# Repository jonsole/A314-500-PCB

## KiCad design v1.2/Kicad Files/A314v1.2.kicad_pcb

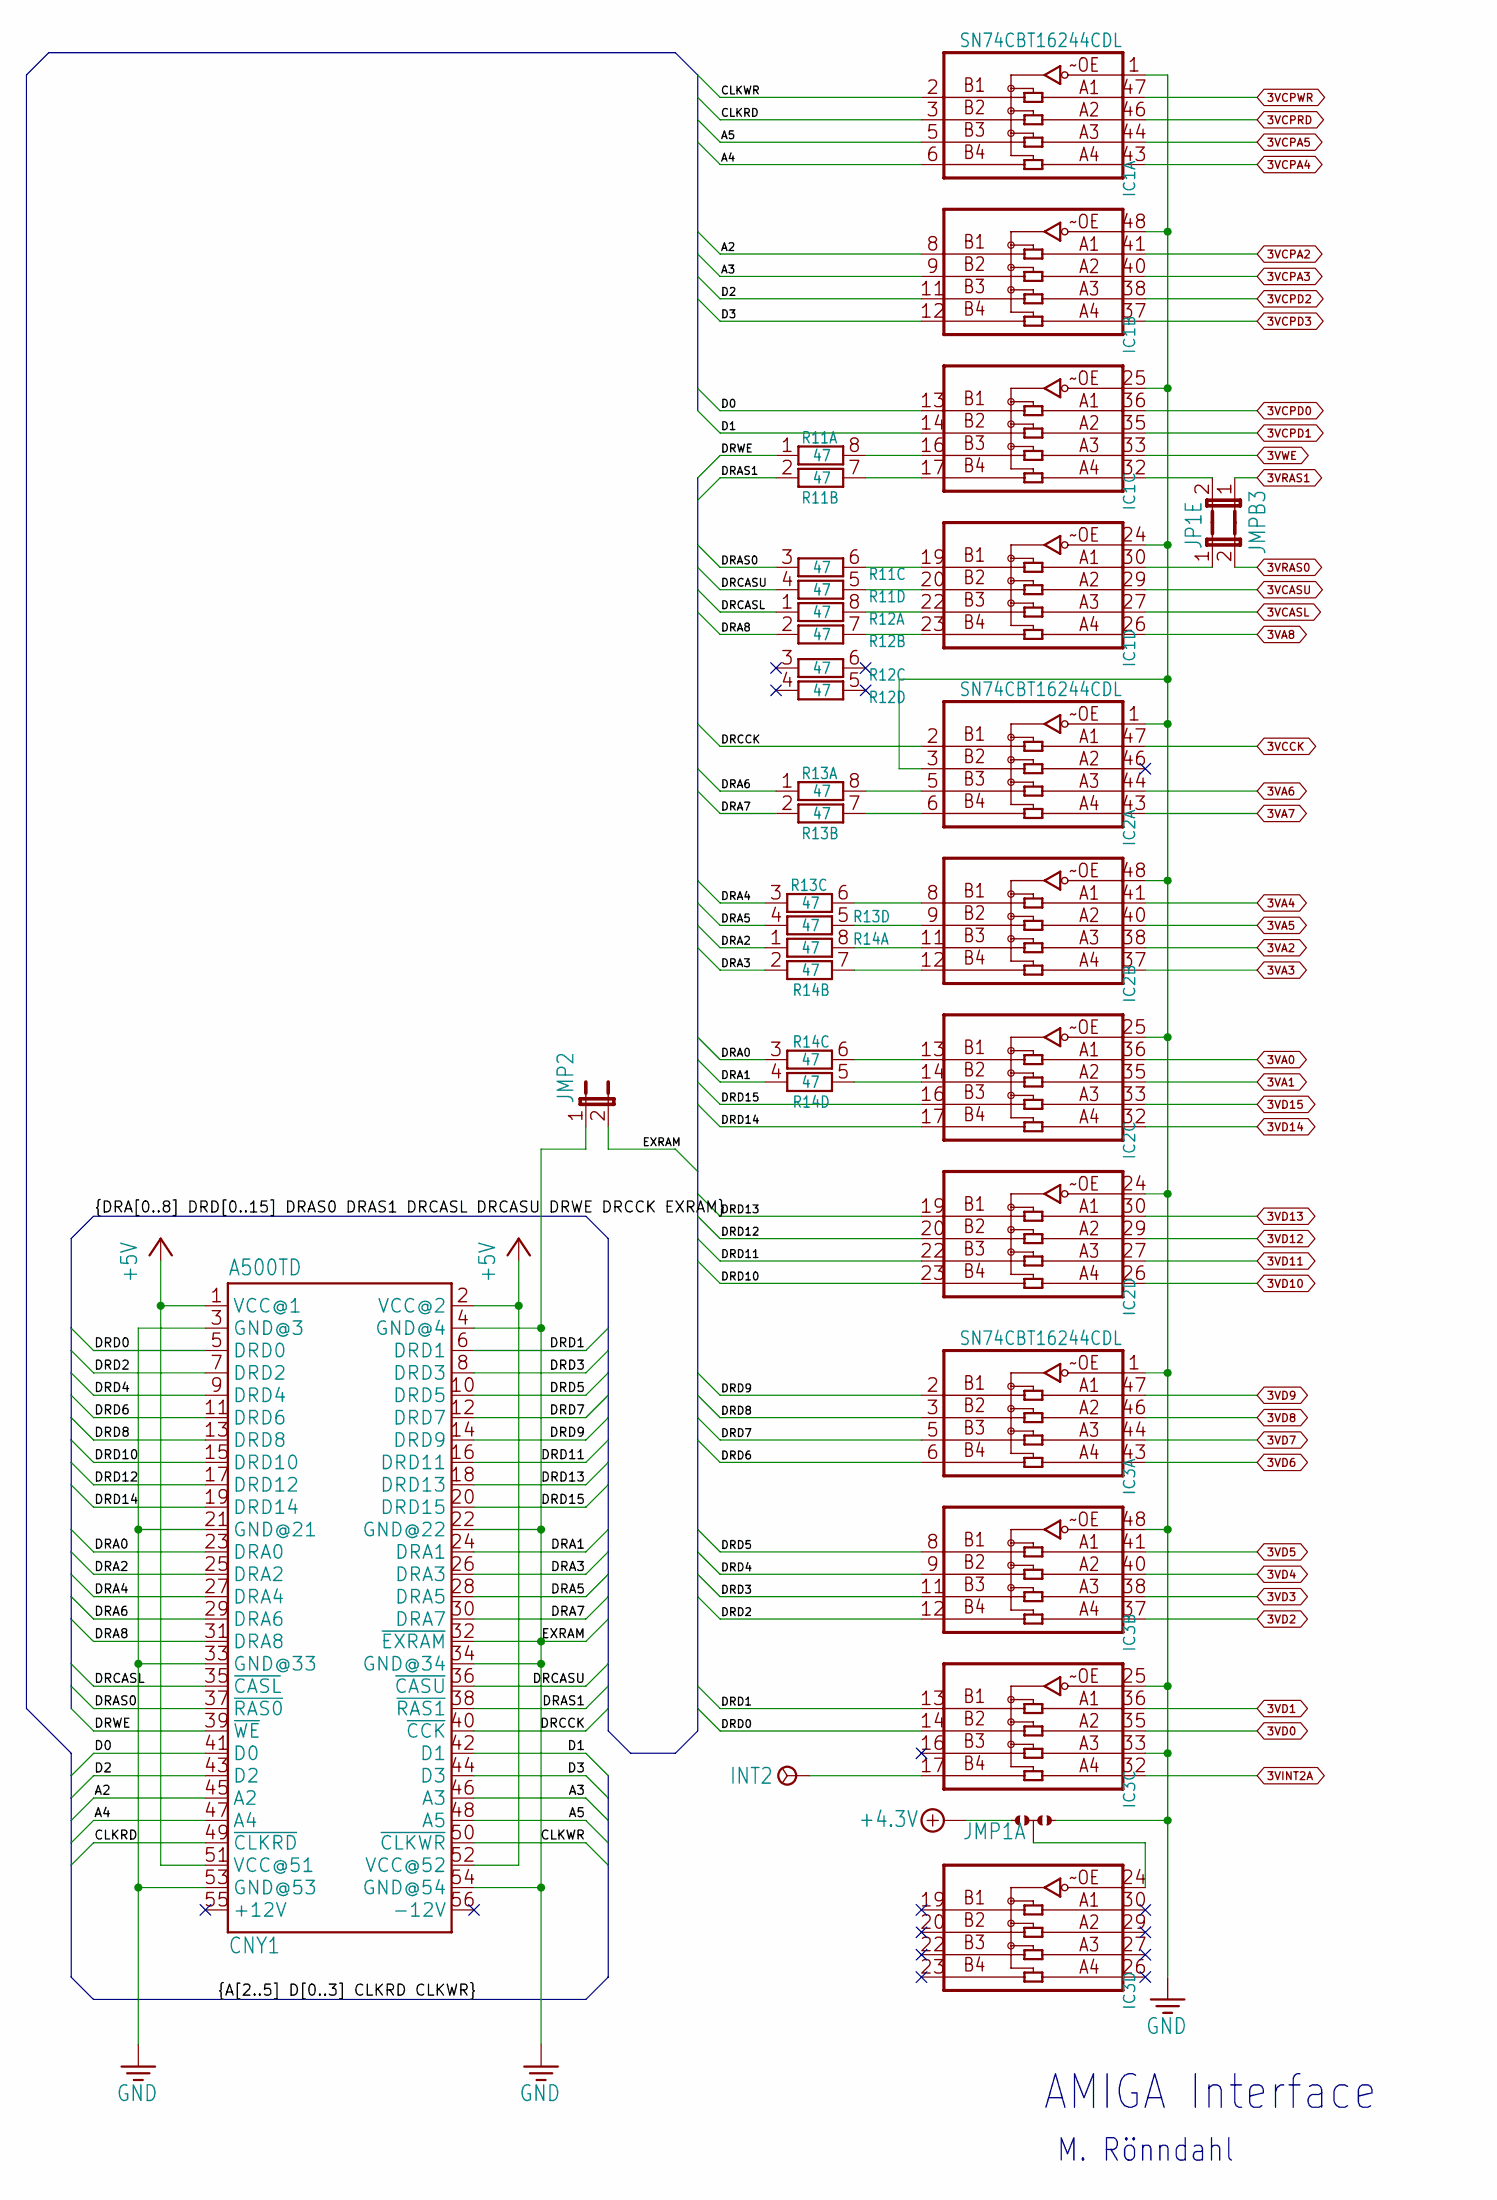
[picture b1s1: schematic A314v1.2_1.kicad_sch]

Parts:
CNY1: A500TD; TRAPDOOR
IC1, IC2, IC3: SN74CBT16244CDL; SSOP-DL48
INT2: TP1; P1-08
JMP1: 0R-JUMPC; C0R-JMP
JMP2: JP1E; JP1
JMP3: RAS0; JP1
JMPB3: JP1E; JP1
R11, R12, R13, R14: 47; CTS742C083

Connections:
3VA0: IC2.36 (A1); also elsewhere on the board
3VA1: IC2.35 (A2); also elsewhere on the board
3VA2: IC2.38 (A3); also elsewhere on the board
3VA3: IC2.37 (A4); also elsewhere on the board
3VA4: IC2.41 (A1); also elsewhere on the board
3VA5: IC2.40 (A2); also elsewhere on the board
3VA6: IC2.44 (A3); also elsewhere on the board
3VA7: IC2.43 (A4); also elsewhere on the board
3VA8: IC1.26 (A4); also elsewhere on the board
3VCASL: IC1.27 (A3); also elsewhere on the board
3VCASU: IC1.29 (A2); also elsewhere on the board
3VCCK: IC2.47 (A1); also elsewhere on the board
3VCPA2: IC1.41 (A1); also elsewhere on the board
3VCPA3: IC1.40 (A2); also elsewhere on the board
3VCPA4: IC1.43 (A4); also elsewhere on the board
3VCPA5: IC1.44 (A3); also elsewhere on the board
3VCPD0: IC1.36 (A1); also elsewhere on the board
3VCPD1: IC1.35 (A2); also elsewhere on the board
3VCPD2: IC1.38 (A3); also elsewhere on the board
3VCPD3: IC1.37 (A4); also elsewhere on the board
3VCPRD: IC1.46 (A2); also elsewhere on the board
3VCPWR: IC1.47 (A1); also elsewhere on the board
3VD0: IC3.35 (A2); also elsewhere on the board
3VD1: IC3.36 (A1); also elsewhere on the board
3VD2: IC3.37 (A4); also elsewhere on the board
3VD3: IC3.38 (A3); also elsewhere on the board
3VD4: IC3.40 (A2); also elsewhere on the board
3VD5: IC3.41 (A1); also elsewhere on the board
3VD6: IC3.43 (A4); also elsewhere on the board
3VD7: IC3.44 (A3); also elsewhere on the board
3VD8: IC3.46 (A2); also elsewhere on the board
3VD9: IC3.47 (A1); also elsewhere on the board
3VD10: IC2.26 (A4); also elsewhere on the board
3VD11: IC2.27 (A3); also elsewhere on the board
3VD12: IC2.29 (A2); also elsewhere on the board
3VD13: IC2.30 (A1); also elsewhere on the board
3VD14: IC2.32 (A4); also elsewhere on the board
3VD15: IC2.33 (A3); also elsewhere on the board
3VINT2A: IC3.32 (A4); also elsewhere on the board
3VRAS0: JMP3.2; also elsewhere on the board
3VRAS1: JMPB3.1; also elsewhere on the board
3VWE: IC1.33 (A3); also elsewhere on the board
+4.3V: JMP1.1; also elsewhere on the board
+5V: CNY1.1 (VCC@1), CNY1.2 (VCC@2), CNY1.51 (VCC@51), CNY1.52 (VCC@52); also elsewhere on the board
/AMIGA Interface/A2: CNY1.45 (A2), IC1.8 (B1)
/AMIGA Interface/A3: CNY1.46 (A3), IC1.9 (B2)
/AMIGA Interface/A4: CNY1.47 (A4), IC1.6 (B4)
/AMIGA Interface/A5: CNY1.48 (A5), IC1.5 (B3)
/AMIGA Interface/CLKRD: CNY1.49 (~CLKRD), IC1.3 (B2)
/AMIGA Interface/CLKWR: CNY1.50 (~CLKWR), IC1.2 (B1)
/AMIGA Interface/D0: CNY1.41 (D0), IC1.13 (B1)
/AMIGA Interface/D1: CNY1.42 (D1), IC1.14 (B2)
/AMIGA Interface/D2: CNY1.43 (D2), IC1.11 (B3)
/AMIGA Interface/D3: CNY1.44 (D3), IC1.12 (B4)
/AMIGA Interface/DRA0: CNY1.23 (DRA0), R14.3
/AMIGA Interface/DRA1: CNY1.24 (DRA1), R14.4
/AMIGA Interface/DRA2: CNY1.25 (DRA2), R14.1
/AMIGA Interface/DRA3: CNY1.26 (DRA3), R14.2
/AMIGA Interface/DRA4: CNY1.27 (DRA4), R13.3
/AMIGA Interface/DRA5: CNY1.28 (DRA5), R13.4
/AMIGA Interface/DRA6: CNY1.29 (DRA6), R13.1
/AMIGA Interface/DRA7: CNY1.30 (DRA7), R13.2
/AMIGA Interface/DRA8: CNY1.31 (DRA8), R12.2
/AMIGA Interface/DRAS0: CNY1.37 (~RAS0), R11.3
/AMIGA Interface/DRAS1: CNY1.38 (~RAS1), R11.2
/AMIGA Interface/DRCASL: CNY1.35 (~CASL), R12.1
/AMIGA Interface/DRCASU: CNY1.36 (~CASU), R11.4
/AMIGA Interface/DRCCK: CNY1.40 (~CCK), IC2.2 (B1)
/AMIGA Interface/DRD0: CNY1.5 (DRD0), IC3.14 (B2)
/AMIGA Interface/DRD1: CNY1.6 (DRD1), IC3.13 (B1)
/AMIGA Interface/DRD2: CNY1.7 (DRD2), IC3.12 (B4)
/AMIGA Interface/DRD3: CNY1.8 (DRD3), IC3.11 (B3)
/AMIGA Interface/DRD4: CNY1.9 (DRD4), IC3.9 (B2)
/AMIGA Interface/DRD5: CNY1.10 (DRD5), IC3.8 (B1)
/AMIGA Interface/DRD6: CNY1.11 (DRD6), IC3.6 (B4)
/AMIGA Interface/DRD7: CNY1.12 (DRD7), IC3.5 (B3)
/AMIGA Interface/DRD8: CNY1.13 (DRD8), IC3.3 (B2)
/AMIGA Interface/DRD9: CNY1.14 (DRD9), IC3.2 (B1)
/AMIGA Interface/DRD10: CNY1.15 (DRD10), IC2.23 (B4)
/AMIGA Interface/DRD11: CNY1.16 (DRD11), IC2.22 (B3)
/AMIGA Interface/DRD12: CNY1.17 (DRD12), IC2.20 (B2)
/AMIGA Interface/DRD13: CNY1.18 (DRD13), IC2.19 (B1)
/AMIGA Interface/DRD14: CNY1.19 (DRD14), IC2.17 (B4)
/AMIGA Interface/DRD15: CNY1.20 (DRD15), IC2.16 (B3)
/AMIGA Interface/DRWE: CNY1.39 (~WE), R11.1
GND: CNY1.3 (GND@3), CNY1.4 (GND@4), CNY1.21 (GND@21), CNY1.22 (GND@22), CNY1.32 (~EXRAM), CNY1.33 (GND@33), CNY1.34 (GND@34), CNY1.53 (GND@53), CNY1.54 (GND@54), IC1.1 (~OE), IC1.24 (~OE), IC1.25 (~OE), IC1.48 (~OE), IC2.1 (~OE), IC2.3 (B2), IC2.24 (~OE), IC2.25 (~OE), IC2.48 (~OE), IC3.1 (~OE), IC3.25 (~OE), IC3.33 (A3), IC3.48 (~OE), JMP1.3, JMP2.1, JMP2.2; also elsewhere on the board
unnamed: IC1.32 (A4), JMPB3.2
unnamed: IC1.16 (B3), R11.8
unnamed: IC1.17 (B4), R11.7
unnamed: IC1.30 (A1), JMP3.1
unnamed: IC1.19 (B1), R11.6
unnamed: IC1.20 (B2), R11.5
unnamed: IC1.22 (B3), R12.8
unnamed: IC1.23 (B4), R12.7
unnamed: IC2.5 (B3), R13.8
unnamed: IC2.6 (B4), R13.7
unnamed: IC2.8 (B1), R13.6
unnamed: IC2.9 (B2), R13.5
unnamed: IC2.11 (B3), R14.8
unnamed: IC2.12 (B4), R14.7
unnamed: IC2.13 (B1), R14.6
unnamed: IC2.14 (B2), R14.5
unnamed: IC3.17 (B4), INT2.TP
unnamed: IC3.24 (~OE), JMP1.2

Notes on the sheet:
M. Rönndahl
AMIGA Interface

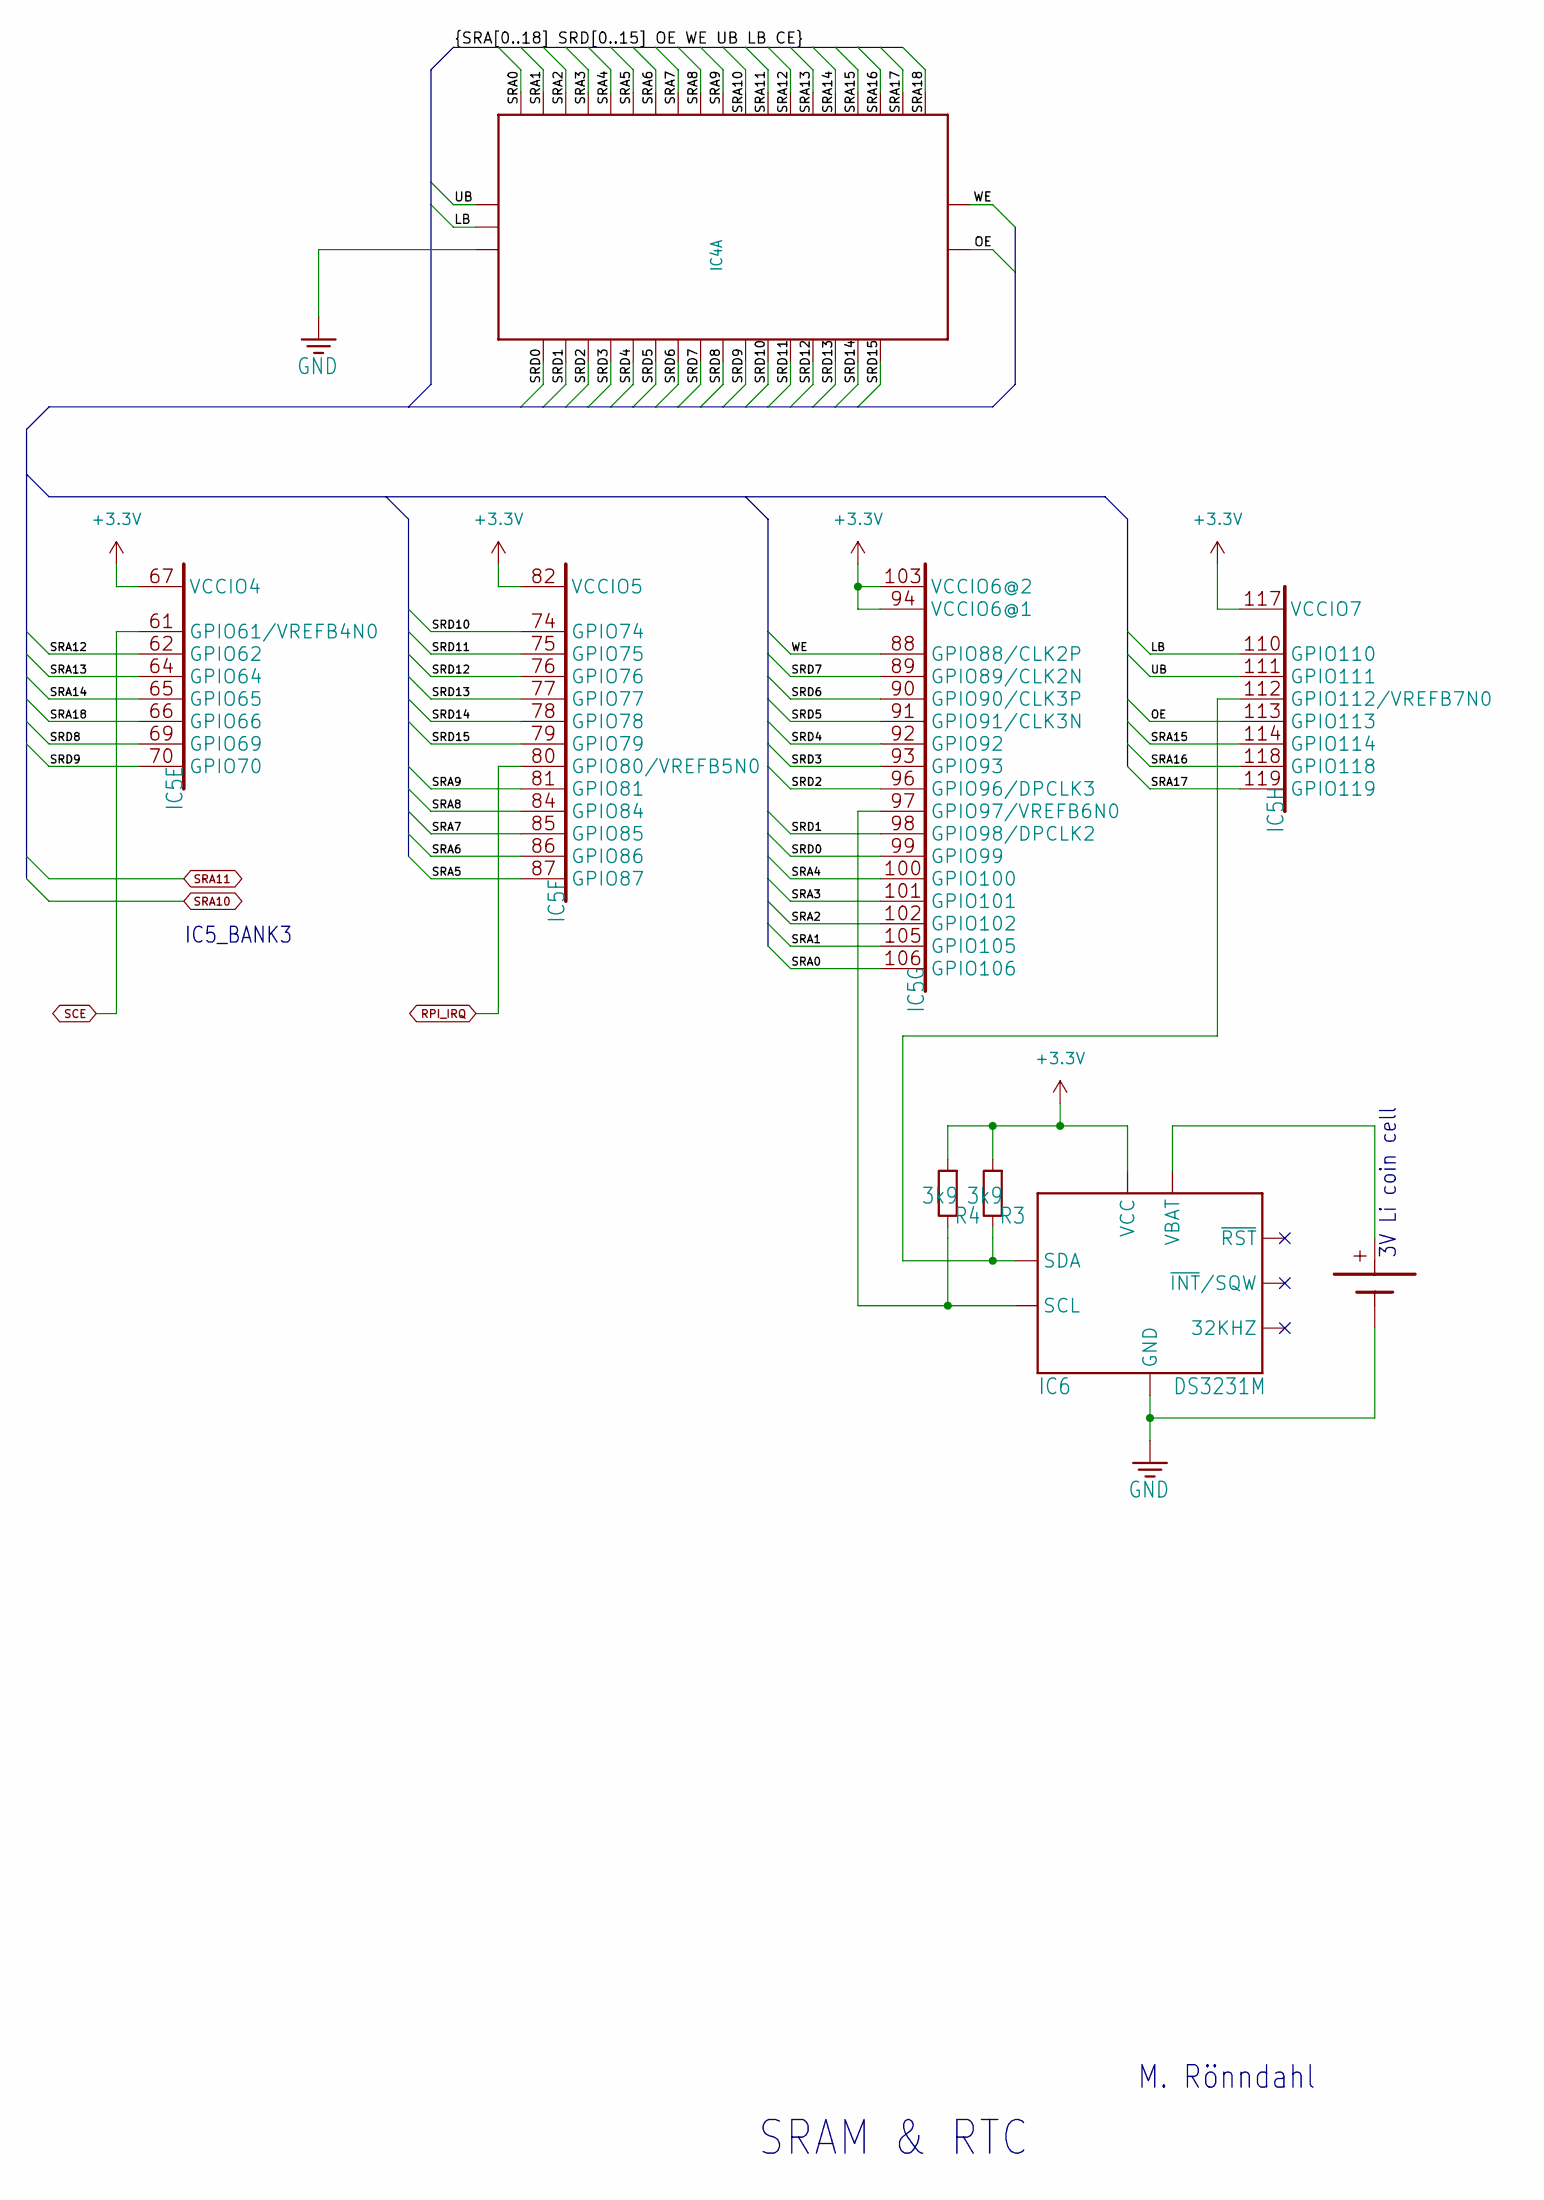
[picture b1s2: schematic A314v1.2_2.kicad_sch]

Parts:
BAT1: CR2025/CR2032TH; LINX20XX-THM
IC4: IS61WV51216BLL-10TLI; TSOP-2
IC5: 10M08SCE144; SQFP-S-20X20-144
IC6: DS3231M; SOIC8
R3, R4: 3k9; R0805

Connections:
+3.3V: IC5.67 (VCCIO4), IC5.82 (VCCIO5), IC5.94 (VCCIO6@1), IC5.103 (VCCIO6@2), IC5.117 (VCCIO7), IC6.2 (VCC), R3.2, R4.2; also elsewhere on the board
/SRAM & RTC/LB: IC4.39 (~LB), IC5.110 (GPIO110)
/SRAM & RTC/OE: IC4.41 (~OE), IC5.113 (GPIO113)
/SRAM & RTC/SRA0: IC4.1 (A0), IC5.106 (GPIO106)
/SRAM & RTC/SRA1: IC4.2 (A1), IC5.105 (GPIO105)
/SRAM & RTC/SRA2: IC4.3 (A2), IC5.102 (GPIO102)
/SRAM & RTC/SRA3: IC4.4 (A3), IC5.101 (GPIO101)
/SRAM & RTC/SRA4: IC4.5 (A4), IC5.100 (GPIO100)
/SRAM & RTC/SRA5: IC4.18 (A5), IC5.87 (GPIO87)
/SRAM & RTC/SRA6: IC4.19 (A6), IC5.86 (GPIO86)
/SRAM & RTC/SRA7: IC4.20 (A7), IC5.85 (GPIO85)
/SRAM & RTC/SRA8: IC4.21 (A8), IC5.84 (GPIO84)
/SRAM & RTC/SRA9: IC4.22 (A9), IC5.81 (GPIO81)
/SRAM & RTC/SRA12: IC4.25 (A12), IC5.62 (GPIO62)
/SRAM & RTC/SRA13: IC4.26 (A13), IC5.64 (GPIO64)
/SRAM & RTC/SRA14: IC4.27 (A14), IC5.65 (GPIO65)
/SRAM & RTC/SRA15: IC4.42 (A15), IC5.114 (GPIO114)
/SRAM & RTC/SRA16: IC4.43 (A16), IC5.118 (GPIO118)
/SRAM & RTC/SRA17: IC4.44 (A17), IC5.119 (GPIO119)
/SRAM & RTC/SRA18: IC4.28 (A18), IC5.66 (GPIO66)
/SRAM & RTC/SRD0: IC4.7 (D0), IC5.99 (GPIO99)
/SRAM & RTC/SRD1: IC4.8 (D1), IC5.98 (GPIO98/DPCLK2)
/SRAM & RTC/SRD2: IC4.9 (D2), IC5.96 (GPIO96/DPCLK3)
/SRAM & RTC/SRD3: IC4.10 (D3), IC5.93 (GPIO93)
/SRAM & RTC/SRD4: IC4.13 (D4), IC5.92 (GPIO92)
/SRAM & RTC/SRD5: IC4.14 (D5), IC5.91 (GPIO91/CLK3N)
/SRAM & RTC/SRD6: IC4.15 (D6), IC5.90 (GPIO90/CLK3P)
/SRAM & RTC/SRD7: IC4.16 (D7), IC5.89 (GPIO89/CLK2N)
/SRAM & RTC/SRD8: IC4.29 (D8), IC5.69 (GPIO69)
/SRAM & RTC/SRD9: IC4.30 (D9), IC5.70 (GPIO70)
/SRAM & RTC/SRD10: IC4.31 (D10), IC5.74 (GPIO74)
/SRAM & RTC/SRD11: IC4.32 (D11), IC5.75 (GPIO75)
/SRAM & RTC/SRD12: IC4.35 (D12), IC5.76 (GPIO76)
/SRAM & RTC/SRD13: IC4.36 (D13), IC5.77 (GPIO77)
/SRAM & RTC/SRD14: IC4.37 (D14), IC5.78 (GPIO78)
/SRAM & RTC/SRD15: IC4.38 (D15), IC5.79 (GPIO79)
/SRAM & RTC/UB: IC4.40 (~UB), IC5.111 (GPIO111)
/SRAM & RTC/WE: IC4.17 (~WE), IC5.88 (GPIO88/CLK2P)
GND: BAT1.GND (-), IC4.6 (~CE), IC6.5 (GND); also elsewhere on the board
unnamed: IC5.97 (GPIO97/VREFB6N0), IC6.8 (SCL), R4.1
unnamed: IC5.112 (GPIO112/VREFB7N0), IC6.7 (SDA), R3.1
unnamed: BAT1.+@1 (+), BAT1.+@2 (+), BAT1.+@3 (+), BAT1.+@4 (+), IC6.6 (VBAT)
RPI_IRQ: IC5.80 (GPIO80/VREFB5N0); also elsewhere on the board
SCE: IC5.61 (GPIO61/VREFB4N0); also elsewhere on the board
SRA10: IC4.23 (A10); also elsewhere on the board
SRA11: IC4.24 (A11); also elsewhere on the board

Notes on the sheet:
SRAM & RTC
3V Li coin cell
M. Rönndahl
IC5_BANK3

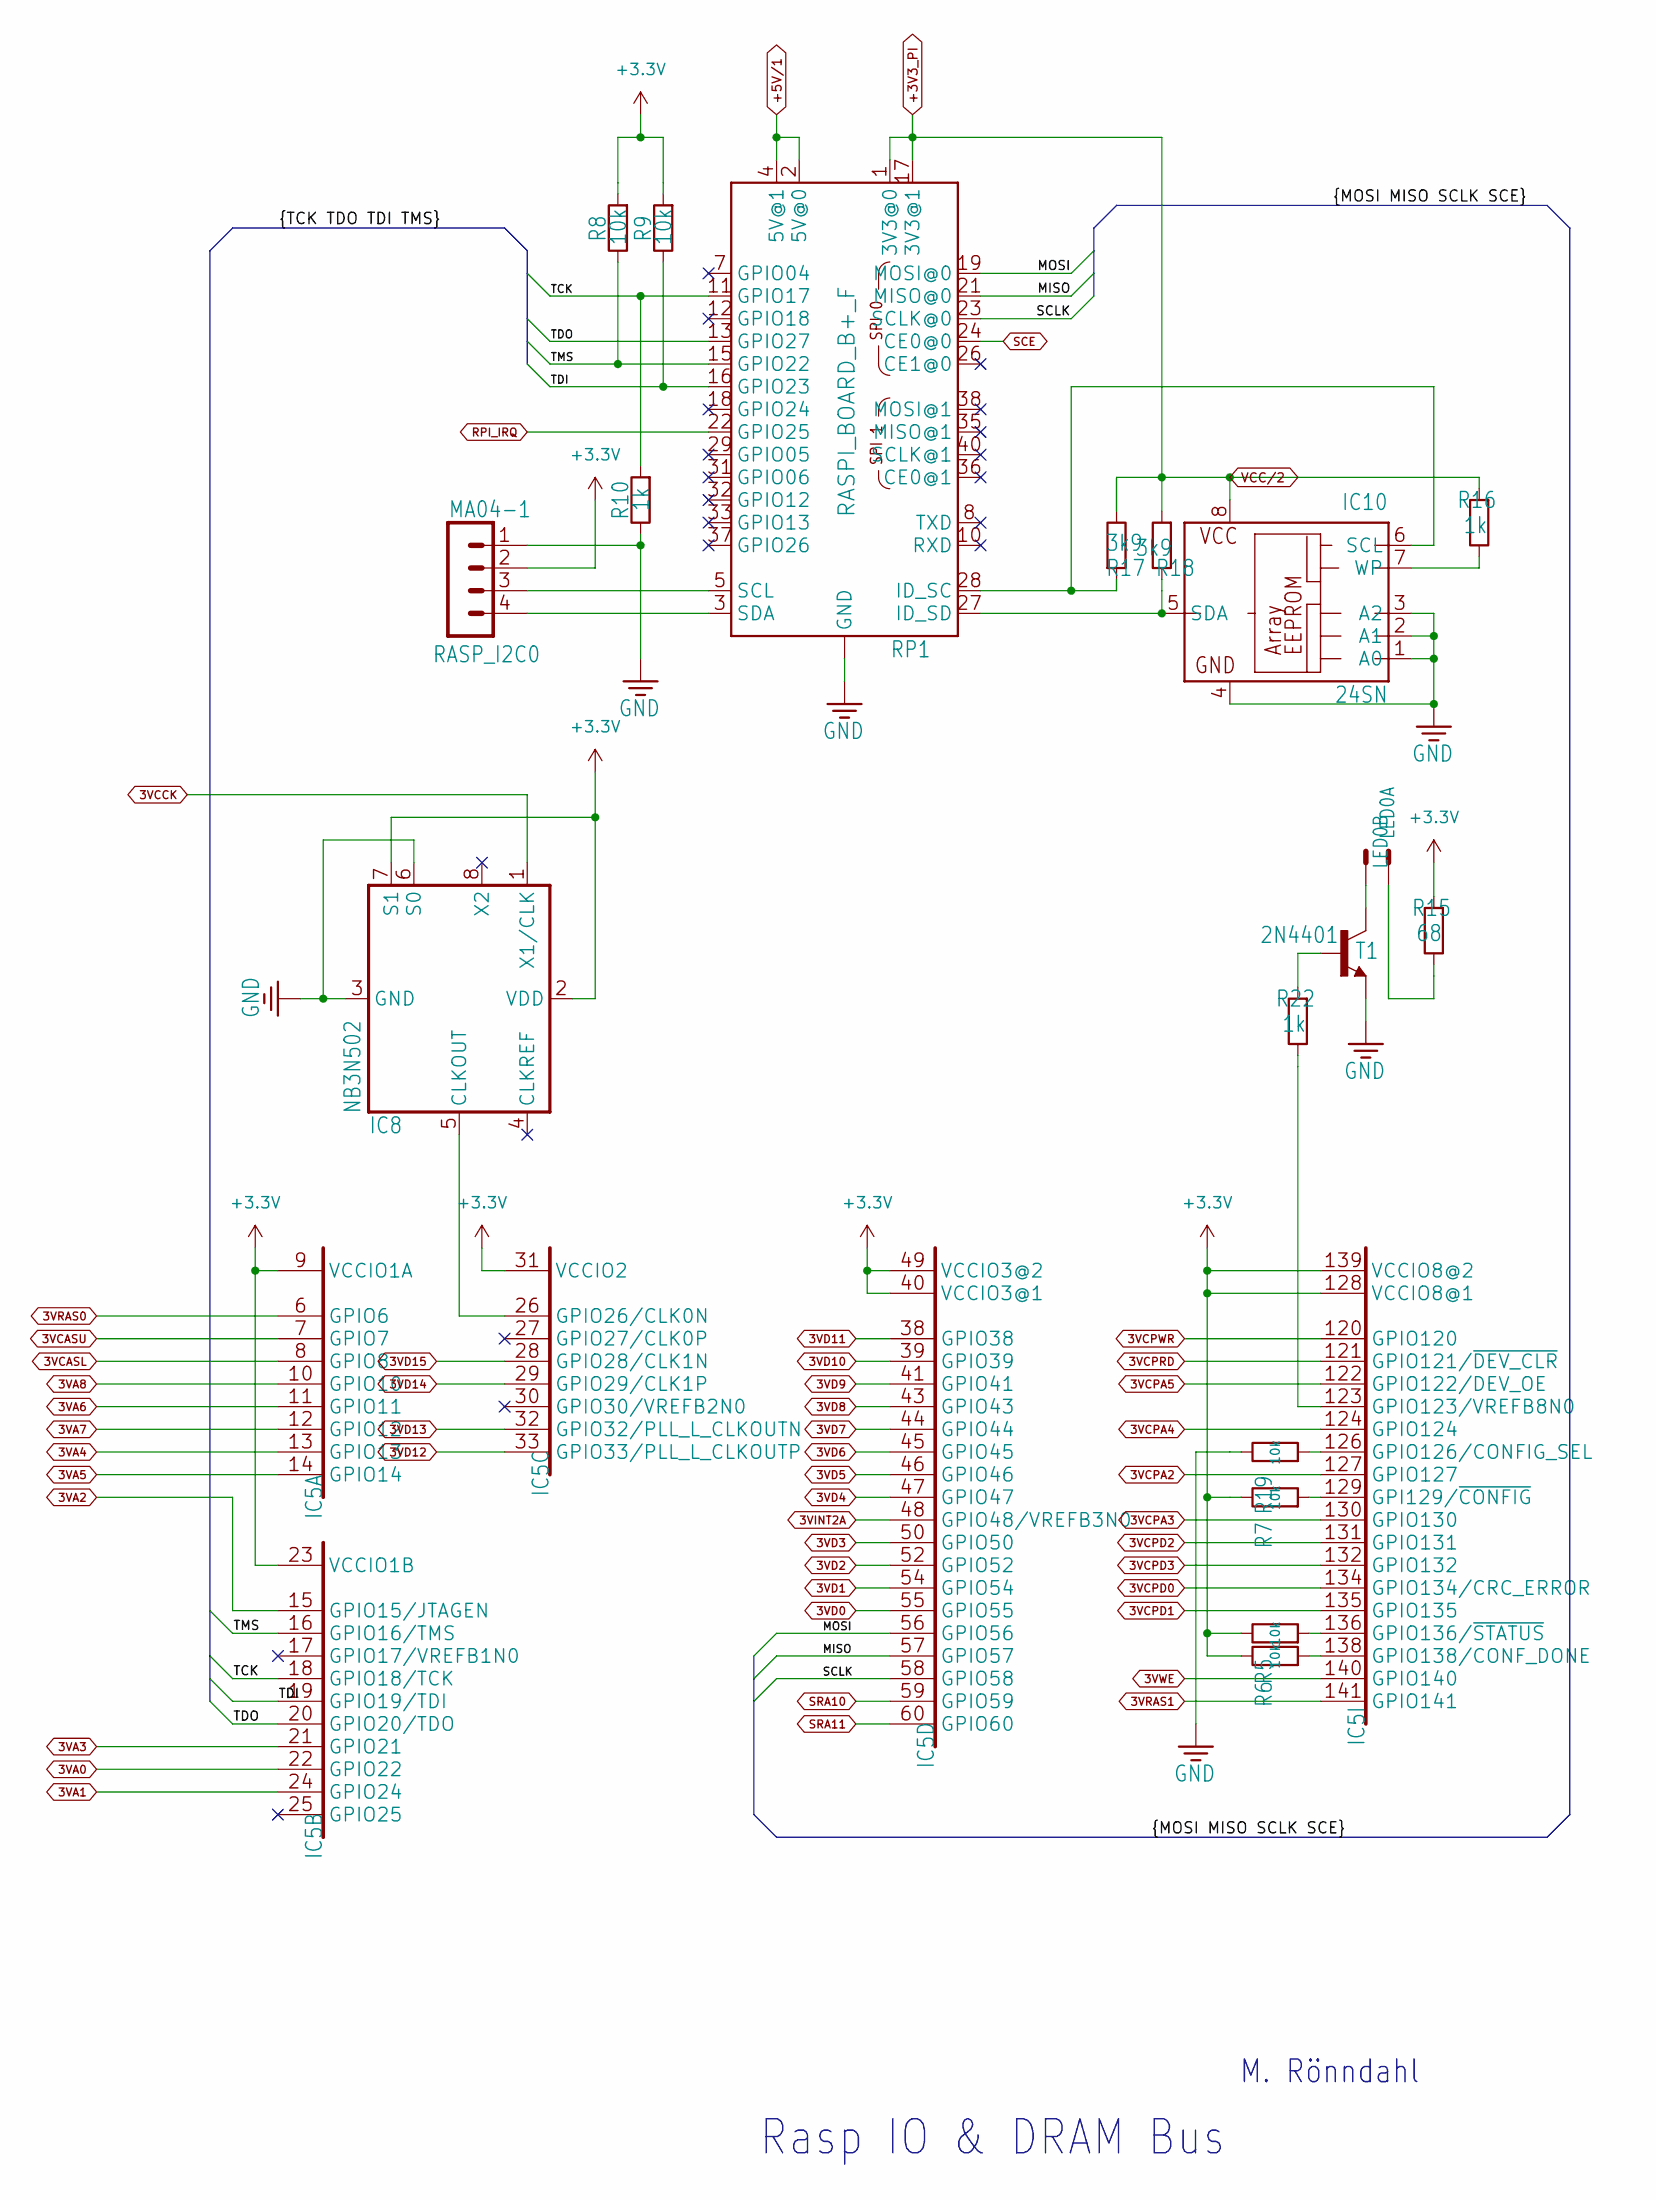
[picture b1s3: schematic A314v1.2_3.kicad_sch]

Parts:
IC5: 10M08SCE144; SQFP-S-20X20-144
IC8: NB3N502; SO08
IC10: 24SN; SO-08
LED0: 22-23-2021
R5, R6, R7, R8, R9, R19: 10k; R0805
R10, R16, R22: 1k; R0805
R15: 68; R0805
R17, R18: 3k9; R0805
RASP_I2C0: MA04-1
RP1: RASPI_BOARD_B+_F; RASPI_BOARD_B+_FULL
T1: 2N4401; SOT23-BEC

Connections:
3VA0: IC5.22 (GPIO22); also elsewhere on the board
3VA1: IC5.24 (GPIO24); also elsewhere on the board
3VA2: IC5.15 (GPIO15/JTAGEN); also elsewhere on the board
3VA3: IC5.21 (GPIO21); also elsewhere on the board
3VA4: IC5.13 (GPIO13); also elsewhere on the board
3VA5: IC5.14 (GPIO14); also elsewhere on the board
3VA6: IC5.11 (GPIO11); also elsewhere on the board
3VA7: IC5.12 (GPIO12); also elsewhere on the board
3VA8: IC5.10 (GPIO10); also elsewhere on the board
3VCASL: IC5.8 (GPIO8); also elsewhere on the board
3VCASU: IC5.7 (GPIO7); also elsewhere on the board
3VCCK: IC8.1 (X1/CLK); also elsewhere on the board
3VCPA2: IC5.127 (GPIO127); also elsewhere on the board
3VCPA3: IC5.130 (GPIO130); also elsewhere on the board
3VCPA4: IC5.124 (GPIO124); also elsewhere on the board
3VCPA5: IC5.122 (GPIO122/DEV_OE); also elsewhere on the board
3VCPD0: IC5.134 (GPIO134/CRC_ERROR); also elsewhere on the board
3VCPD1: IC5.135 (GPIO135); also elsewhere on the board
3VCPD2: IC5.131 (GPIO131); also elsewhere on the board
3VCPD3: IC5.132 (GPIO132); also elsewhere on the board
3VCPRD: IC5.121 (GPIO121/~DEV_CLR); also elsewhere on the board
3VCPWR: IC5.120 (GPIO120); also elsewhere on the board
3VD0: IC5.55 (GPIO55); also elsewhere on the board
3VD1: IC5.54 (GPIO54); also elsewhere on the board
3VD2: IC5.52 (GPIO52); also elsewhere on the board
3VD3: IC5.50 (GPIO50); also elsewhere on the board
3VD4: IC5.47 (GPIO47); also elsewhere on the board
3VD5: IC5.46 (GPIO46); also elsewhere on the board
3VD6: IC5.45 (GPIO45); also elsewhere on the board
3VD7: IC5.44 (GPIO44); also elsewhere on the board
3VD8: IC5.43 (GPIO43); also elsewhere on the board
3VD9: IC5.41 (GPIO41); also elsewhere on the board
3VD10: IC5.39 (GPIO39); also elsewhere on the board
3VD11: IC5.38 (GPIO38); also elsewhere on the board
3VD12: IC5.33 (GPIO33/PLL_L_CLKOUTP); also elsewhere on the board
3VD13: IC5.32 (GPIO32/PLL_L_CLKOUTN); also elsewhere on the board
3VD14: IC5.29 (GPIO29/CLK1P); also elsewhere on the board
3VD15: IC5.28 (GPIO28/CLK1N); also elsewhere on the board
3VINT2A: IC5.48 (GPIO48/VREFB3N0); also elsewhere on the board
3VRAS0: IC5.6 (GPIO6); also elsewhere on the board
3VRAS1: IC5.141 (GPIO141); also elsewhere on the board
3VWE: IC5.140 (GPIO140); also elsewhere on the board
+3.3V: IC5.9 (VCCIO1A), IC5.23 (VCCIO1B), IC5.31 (VCCIO2), IC5.40 (VCCIO3@1), IC5.49 (VCCIO3@2), IC5.128 (VCCIO8@1), IC5.139 (VCCIO8@2), IC8.2 (VDD), IC8.7 (S1), R5.1, R6.1, R7.1, R8.2, R9.2, R15.2, RASP_I2C0.2; also elsewhere on the board
+3V3_PI: IC10.8 (VCC), R16.2, R17.1, R18.2, RP1.1 (3V3@0), RP1.17 (3V3@1); also elsewhere on the board
+5V/1: RP1.2 (5V@0), RP1.4 (5V@1); also elsewhere on the board
/Raspberry & DRAM Bus/MISO: IC5.57 (GPIO57), RP1.21 (MISO@0)
/Raspberry & DRAM Bus/MOSI: IC5.56 (GPIO56), RP1.19 (MOSI@0)
/Raspberry & DRAM Bus/SCLK: IC5.58 (GPIO58), RP1.23 (SCLK@0)
/Raspberry & DRAM Bus/TCK: IC5.18 (GPIO18/TCK), R10.2, RP1.11 (GPIO17)
/Raspberry & DRAM Bus/TDI: IC5.19 (GPIO19/TDI), R9.1, RP1.16 (GPIO23)
/Raspberry & DRAM Bus/TDO: IC5.20 (GPIO20/TDO), RP1.13 (GPIO27)
/Raspberry & DRAM Bus/TMS: IC5.16 (GPIO16/TMS), R8.1, RP1.15 (GPIO22)
GND: IC8.3 (GND), IC8.6 (S0), IC10.1 (A0), IC10.2 (A1), IC10.3 (A2), IC10.4 (GND), R10.1, R19.1, RASP_I2C0.1, RP1.6 (GND), RP1.9 (GND), RP1.14 (GND), RP1.20 (GND), RP1.25 (GND), RP1.30 (GND), RP1.34 (GND), RP1.39 (GND), T1.E; also elsewhere on the board
unnamed: IC5.26 (GPIO26/CLK0N), IC8.5 (CLKOUT)
unnamed: IC5.129 (GPI129/~CONFIG), R7.2
unnamed: IC5.123 (GPIO123/VREFB8N0), R22.1
unnamed: IC5.126 (GPIO126/CONFIG_SEL), R19.2
unnamed: IC5.136 (GPIO136/~STATUS), R5.2
unnamed: IC5.138 (GPIO138/CONF_DONE), R6.2
unnamed: IC10.6 (SCL), R17.2, RP1.28 (ID_SC)
unnamed: IC10.5 (SDA), R18.1, RP1.27 (ID_SD)
unnamed: IC10.7 (WP), R16.1
unnamed: LED0.1 (S), R15.1
unnamed: LED0.2 (S), T1.C
unnamed: R22.2, T1.B
unnamed: RASP_I2C0.3, RP1.5 (SCL)
unnamed: RASP_I2C0.4, RP1.3 (SDA)
RPI_IRQ: RP1.22 (GPIO25); also elsewhere on the board
SCE: RP1.24 (CE0@0); also elsewhere on the board
SRA10: IC5.59 (GPIO59); also elsewhere on the board
SRA11: IC5.60 (GPIO60); also elsewhere on the board

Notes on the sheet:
M. Rönndahl
Rasp IO & DRAM Bus

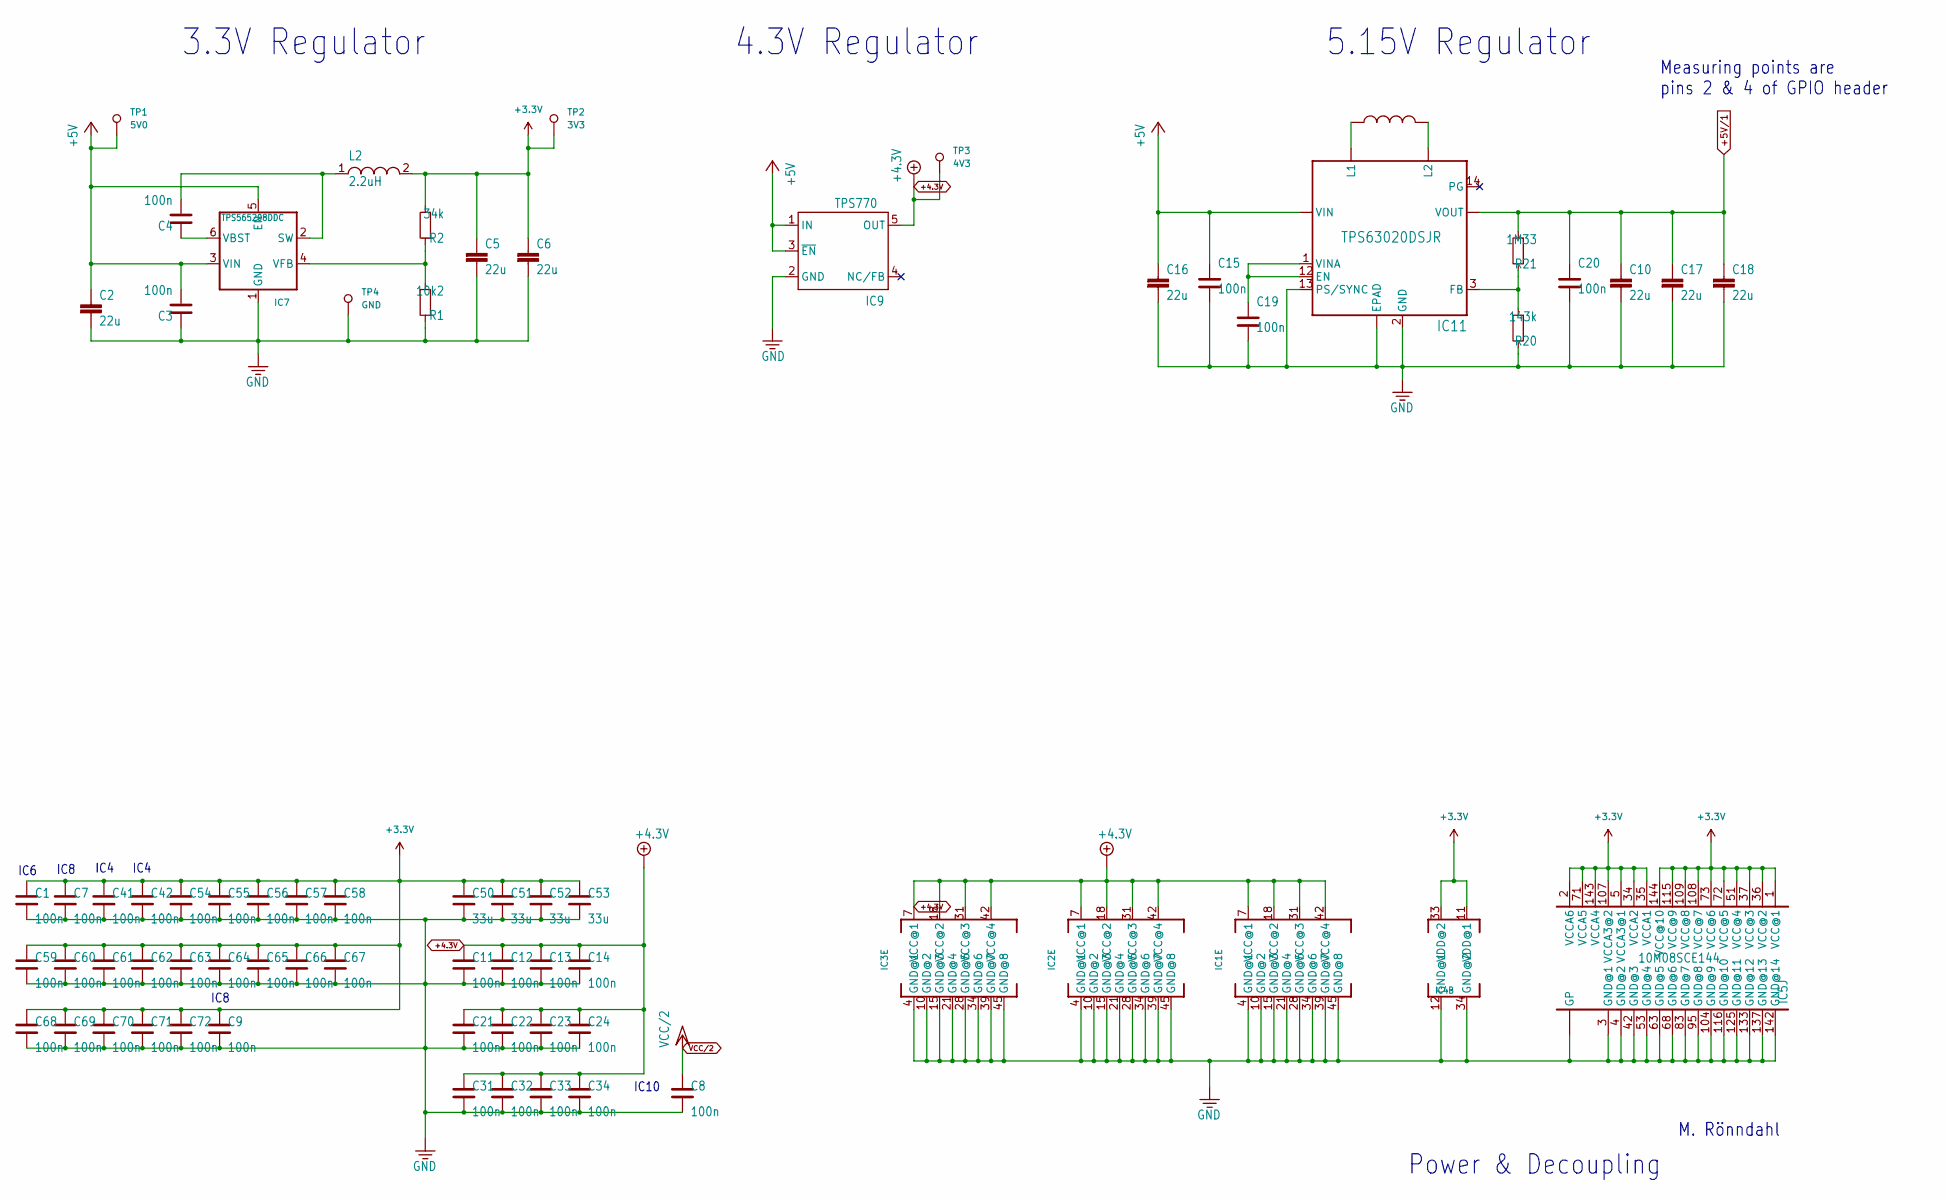
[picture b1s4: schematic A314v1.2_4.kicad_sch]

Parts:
C1, C3, C4, C7, C8, C9, C11, C12, C13, C14, C15, C19, C20, C21, C22, C23, C24, C31, C32, C33, C34, C41, C42, C54, C55, C56, C57, C58, C59, C60, C61, C62, C63, C64, C65, C66, C67, C68, C69, C70, C71, C72: 100n; C_0805_2012Metric_Pad1.18x1.45mm_HandSolder
C2, C5, C6, C10, C16, C17, C18: 22u; C_1812_4532Metric_Pad1.57x3.40mm_HandSolder; MOUSER 810-CGA8P1X7R1E226M
C50, C51, C52, C53: 33u; C_0805_2012Metric_Pad1.18x1.45mm_HandSolder
IC1, IC2, IC3: SN74CBT16244CDL; SSOP-DL48
IC4: IS61WV51216BLL-10TLI; TSOP-2
IC5: 10M08SCE144; SQFP-S-20X20-144
IC7: TPS565208DDC; THIN_SO23; MOUSER 595-TPS565208DDCR
IC9: TPS770; SOT23-DBV
IC11: TPS63020DSJR; DSJ14_2P85X1P58
L1: 1uH; WE-TPC_6823
L2: 2.2uH; WE-TPC_1028_1038; MOUSER 710-7440650022
R1: 10k2; R0805
R2: 34k; R0805
R20: 143k; R0805
R21: 1M33; R0805
TP1: 5V0
TP2: 3V3
TP3: 4V3
TP4: GND

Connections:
+3.3V: C1.1, C5.1, C6.1, C7.1, C9.1, C41.1, C42.1, C50.1, C51.1, C52.1, C53.1, C54.1, C55.1, C56.1, C57.1, C58.1, C59.1, C60.1, C61.1, C62.1, C63.1, C64.1, C65.1, C66.1, C67.1, C68.1, C69.1, C70.1, C71.1, C72.1, IC4.11 (VDD@1), IC4.33 (VDD@2), IC5.1 (VCC@1), IC5.2 (VCCA6), IC5.5 (VCCA3@1), IC5.34 (VCCA2), IC5.35 (VCCA1), IC5.36 (VCC@2), IC5.37 (VCC@3), IC5.51 (VCC@4), IC5.71 (VCCA5), IC5.72 (VCC@5), IC5.73 (VCC@6), IC5.107 (VCCA3@2), IC5.108 (VCC@7), IC5.109 (VCC@8), IC5.115 (VCC@9), IC5.143 (VCCA4), IC5.144 (VCC@10), L2.2, R2.2, TP2.1; also elsewhere on the board
+3V3_PI: C8.1; also elsewhere on the board
+4.3V: C11.1, C12.1, C13.1, C14.1, C21.1, C22.1, C23.1, C24.1, C31.1, C32.1, C33.1, C34.1, IC1.7 (VCC@1), IC1.18 (VCC@2), IC1.31 (VCC@3), IC1.42 (VCC@4), IC2.7 (VCC@1), IC2.18 (VCC@2), IC2.31 (VCC@3), IC2.42 (VCC@4), IC3.7 (VCC@1), IC3.18 (VCC@2), IC3.31 (VCC@3), IC3.42 (VCC@4), IC9.5 (OUT), TP3.1; also elsewhere on the board
+5V: C2.1, C3.2, C15.2, C16.1, IC7.3 (VIN), IC7.5 (EN), IC9.1 (IN), IC9.3 (~EN), IC11.10 (VIN), IC11.11 (VIN), TP1.1; also elsewhere on the board
+5V/1: C10.1, C17.1, C18.1, C20.2, IC11.4 (VOUT), IC11.5 (VOUT), R21.2; also elsewhere on the board
GND: C1.2, C2.2, C3.1, C5.2, C6.2, C7.2, C8.2, C9.2, C10.2, C11.2, C12.2, C13.2, C14.2, C15.1, C16.2, C17.2, C18.2, C19.1, C20.1, C21.2, C22.2, C23.2, C24.2, C31.2, C32.2, C33.2, C34.2, C41.2, C42.2, C50.2, C51.2, C52.2, C53.2, C54.2, C55.2, C56.2, C57.2, C58.2, C59.2, C60.2, C61.2, C62.2, C63.2, C64.2, C65.2, C66.2, C67.2, C68.2, C69.2, C70.2, C71.2, C72.2, IC1.4 (GND@1), IC1.10 (GND@2), IC1.15 (GND@3), IC1.21 (GND@4), IC1.28 (GND@5), IC1.34 (GND@6), IC1.39 (GND@7), IC1.45 (GND@8), IC2.4 (GND@1), IC2.10 (GND@2), IC2.15 (GND@3), IC2.21 (GND@4), IC2.28 (GND@5), IC2.34 (GND@6), IC2.39 (GND@7), IC2.45 (GND@8), IC3.4 (GND@1), IC3.10 (GND@2), IC3.15 (GND@3), IC3.21 (GND@4), IC3.28 (GND@5), IC3.34 (GND@6), IC3.39 (GND@7), IC3.45 (GND@8), IC4.12 (GND@1), IC4.34 (GND@2), IC5.3 (GND@1), IC5.4 (GND@2), IC5.42 (GND@3), IC5.53 (GND@4), IC5.63 (GND@5), IC5.68 (GND@6), IC5.83 (GND@7), IC5.95 (GND@8), IC5.104 (GND@9), IC5.116 (GND@10), IC5.125 (GND@11), IC5.133 (GND@12), IC5.137 (GND@13), IC5.142 (GND@14), IC5.GB@4 (GP), IC5.GP@1 (GP), IC5.GP@2 (GP), IC5.GP@3 (GP), IC5.GP@5 (GP), IC7.1 (GND), IC9.2 (GND), IC11.2 (GND), IC11.13 (PS/SYNC), IC11.15 (EPAD), IC11.V_1 (EPAD), IC11.V_2 (EPAD), IC11.V_3 (EPAD), IC11.V_4 (EPAD), IC11.V_5 (EPAD), R1.1, R20.1, TP4.1; also elsewhere on the board
unnamed: C4.2, IC7.2 (SW), L2.1
unnamed: C4.1, IC7.6 (VBST)
unnamed: IC7.4 (VFB), R1.2, R2.1
unnamed: C19.2, IC11.1 (VINA), IC11.12 (EN)
unnamed: IC11.3 (FB), R20.2, R21.1
unnamed: IC11.8 (L1), IC11.9 (L1), L1.1
unnamed: IC11.6 (L2), IC11.7 (L2), L1.2

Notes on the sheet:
3.3V Regulator
IC10
IC4
Power & Decoupling
4.3V Regulator
M. Rönndahl
IC8
IC6
5.15V Regulator
Measuring points are pins 2 & 4 of GPIO header
